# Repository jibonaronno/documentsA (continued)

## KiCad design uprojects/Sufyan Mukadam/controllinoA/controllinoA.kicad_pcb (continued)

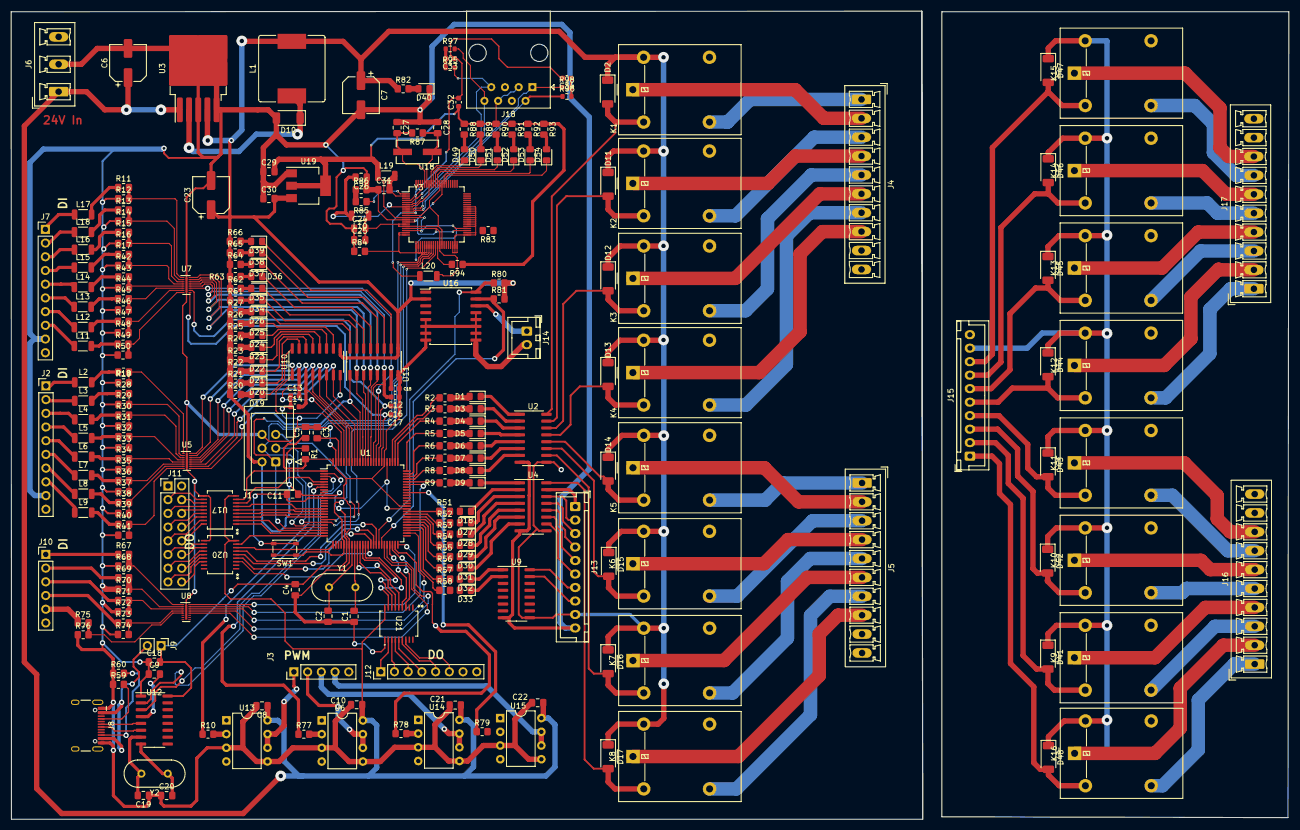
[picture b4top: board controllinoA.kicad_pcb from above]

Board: 2 copper layers, 168.9 x 149.7 mm, 265 parts (0 on the bottom side), 321 nets.

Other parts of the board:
C32: 0.1uF; C_0603_1608Metric
R95, R97: 49.9; R_0603_1608Metric
U21: TBD62783AFNG_EL; SSOP18-P-225-0p65_TOS

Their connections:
24V: U21.9 (VCC); also elsewhere on the board

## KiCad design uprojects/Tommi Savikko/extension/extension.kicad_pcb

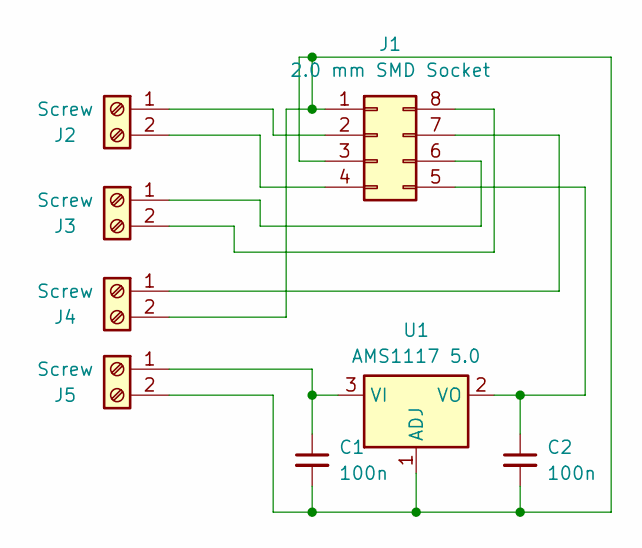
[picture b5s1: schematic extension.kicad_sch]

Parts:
C1, C2: 100n; C_0603_1608Metric
J1: 2.0 mm SMD Socket; PinSocket_2x04_P2.00mm_Vertical_SMD
J2, J3, J4, J5: Screw; WAGO_2060-452_998-404
U1: AMS1117 5.0; SOT-223-3_TabPin2

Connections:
unnamed: C1.2, C2.2, J1.1, J1.3, J4.2, J5.2, U1.1 (ADJ)
unnamed: J1.2, J2.1
unnamed: J1.4, J2.2
unnamed: C2.1, J1.5, U1.2 (VO)
unnamed: J1.6, J3.1
unnamed: J1.7, J4.1
unnamed: J1.8, J3.2
unnamed: C1.1, J5.1, U1.3 (VI)

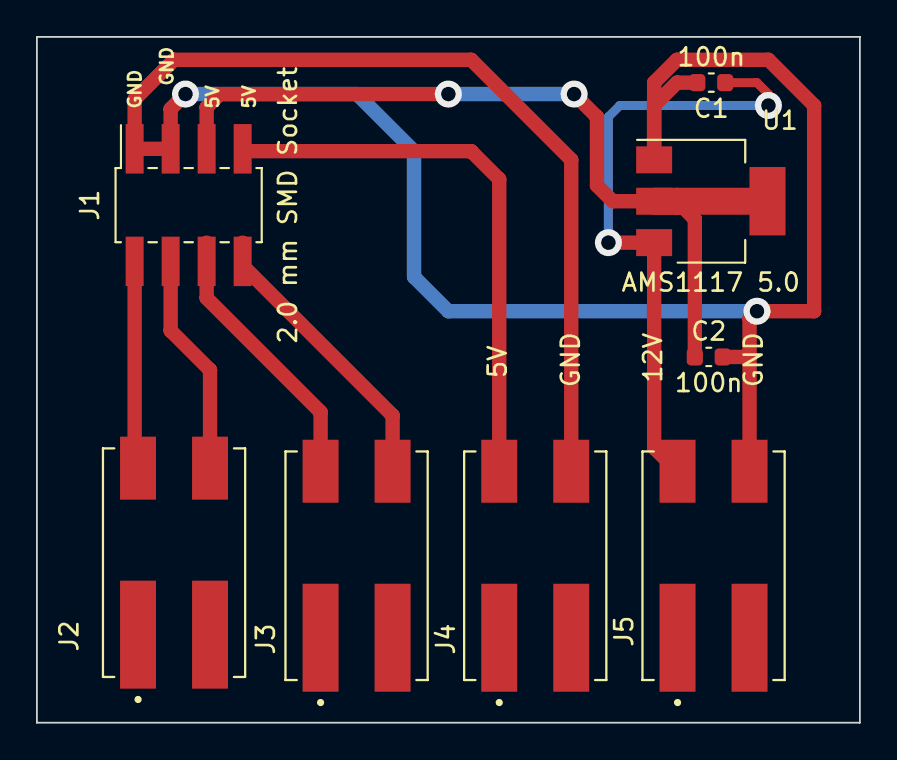
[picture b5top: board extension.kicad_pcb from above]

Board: 2 copper layers, 45.7 x 38.1 mm, 8 parts (0 on the bottom side), 8 nets.

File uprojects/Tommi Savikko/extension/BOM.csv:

Source:,E:\documentsA\uprojects\Tommi Savikko\extension\extension.kicad_sch,,,,,,
Date:,12/16/2023 14:11,,,,,,
Tool:,Eeschema 7.0.9,,,,,,
Generator:,C:\Program Files\KiCad\7.0\bin\scripting\plugins/bom_csv_grouped_by_value.py,,,,,,
Component Count:,8,,,,,,
,,,,,,,
Collated Components:,,,,,,,
,,,,,,,
Item,Qty,Reference(s),Value,LibPart,Footprint,Datasheet,DNP
1,2,"C1, C2",100n,Device:C_Small,Capacitor_SMD:C_0603_1608Metric,~,
2,1,J1,2.0 mm SMD Socket,Connector_Generic:Conn_02x04_Counter_Clockwise,Connector_PinSocket_2.00mm:PinSocket_2x04_P2.00mm_Vertical_SMD,~,
3,4,"J2, J3, J4, J5",Screw,Connector:Screw_Terminal_01x02,wago_smd_2screw:WAGO_2060-452_998-404,~,
4,1,U1,AMS1117 5.0,Regulator_Linear:AMS1117,Package_TO_SOT_SMD:SOT-223-3_TabPin2,http://www.advanced-monolithic.com/pdf/ds1117.pdf,
